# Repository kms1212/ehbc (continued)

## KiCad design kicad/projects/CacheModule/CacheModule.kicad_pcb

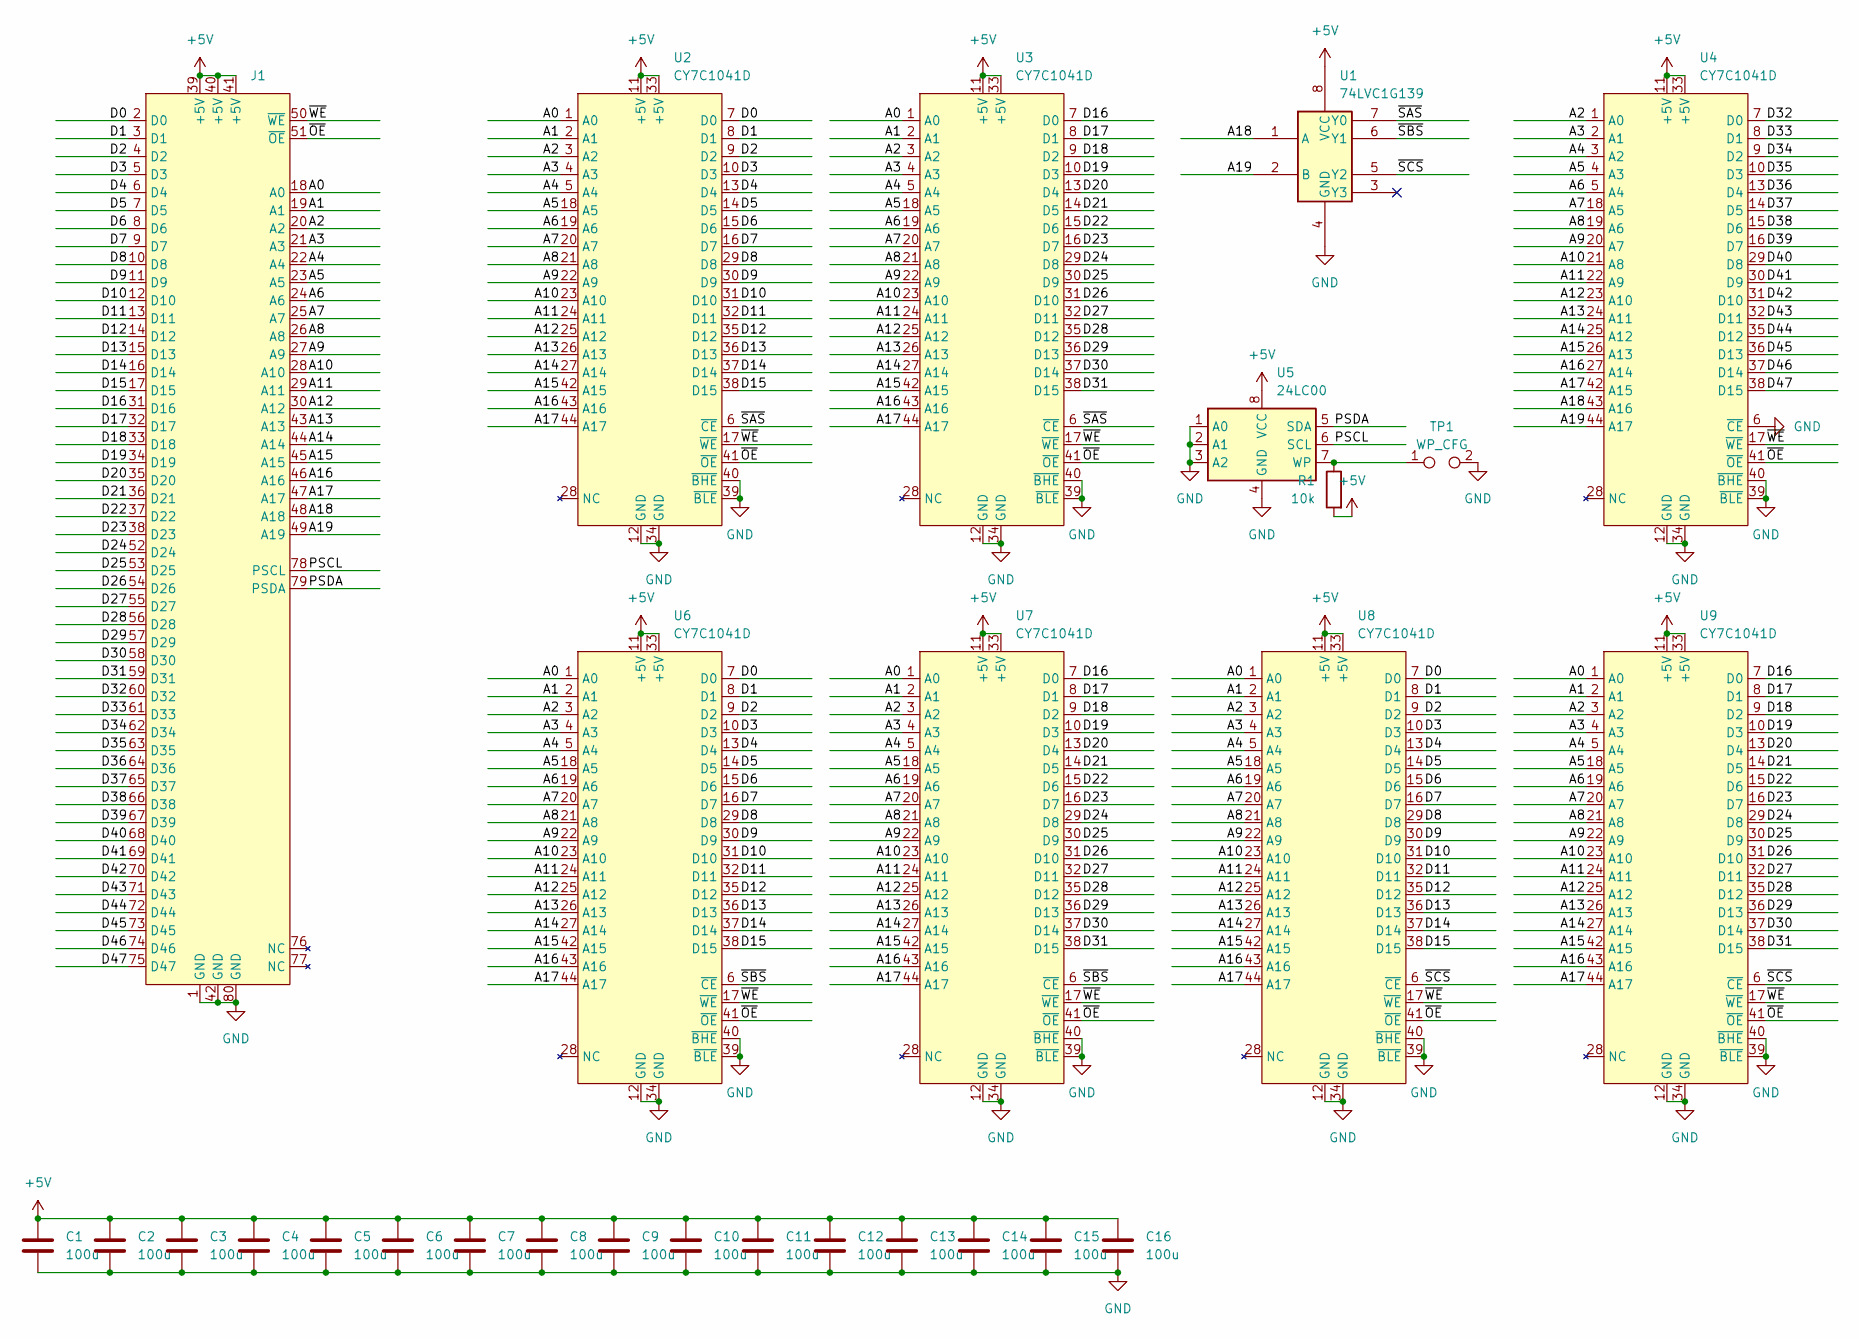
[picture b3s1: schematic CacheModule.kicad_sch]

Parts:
C1, C2, C3, C4, C5, C6, C7, C8, C9, C10, C11, C12, C13, C14, C15, C16: 100u; C_0603_1608Metric_Pad1.08x0.95mm_HandSolder
J1: SIMM80_CardEdge
R1: 10k; R_0603_1608Metric_Pad0.98x0.95mm_HandSolder
TP1: WP_CFG; R_0402_1005Metric
U1: 74LVC1G139; SSOP-8_3.9x5.05mm_P1.27mm
U2, U3, U4, U6, U7, U8, U9: CY7C1041D; TSOP-II-44_10.16x18.41mm_P0.8mm
U5: 24LC00; SOIC-8_3.9x4.9mm_P1.27mm

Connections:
+5V: C1.1, C2.1, C3.1, C4.1, C5.1, C6.1, C7.1, C8.1, C9.1, C10.1, C11.1, C12.1, C13.1, C14.1, C15.1, C16.1, J1.39 (+5V), J1.40 (+5V), J1.41 (+5V), R1.2, U1.8 (VCC), U2.11 (+5V), U2.33 (+5V), U3.11 (+5V), U3.33 (+5V), U4.11 (+5V), U4.33 (+5V), U5.8 (VCC), U6.11 (+5V), U6.33 (+5V), U7.11 (+5V), U7.33 (+5V), U8.11 (+5V), U8.33 (+5V), U9.11 (+5V), U9.33 (+5V)
/A0: J1.18 (A0), U2.1 (A0), U3.1 (A0), U6.1 (A0), U7.1 (A0), U8.1 (A0), U9.1 (A0)
/A1: J1.19 (A1), U2.2 (A1), U3.2 (A1), U6.2 (A1), U7.2 (A1), U8.2 (A1), U9.2 (A1)
/A2: J1.20 (A2), U2.3 (A2), U3.3 (A2), U4.1 (A0), U6.3 (A2), U7.3 (A2), U8.3 (A2), U9.3 (A2)
/A3: J1.21 (A3), U2.4 (A3), U3.4 (A3), U4.2 (A1), U6.4 (A3), U7.4 (A3), U8.4 (A3), U9.4 (A3)
/A4: J1.22 (A4), U2.5 (A4), U3.5 (A4), U4.3 (A2), U6.5 (A4), U7.5 (A4), U8.5 (A4), U9.5 (A4)
/A5: J1.23 (A5), U2.18 (A5), U3.18 (A5), U4.4 (A3), U6.18 (A5), U7.18 (A5), U8.18 (A5), U9.18 (A5)
/A6: J1.24 (A6), U2.19 (A6), U3.19 (A6), U4.5 (A4), U6.19 (A6), U7.19 (A6), U8.19 (A6), U9.19 (A6)
/A7: J1.25 (A7), U2.20 (A7), U3.20 (A7), U4.18 (A5), U6.20 (A7), U7.20 (A7), U8.20 (A7), U9.20 (A7)
/A8: J1.26 (A8), U2.21 (A8), U3.21 (A8), U4.19 (A6), U6.21 (A8), U7.21 (A8), U8.21 (A8), U9.21 (A8)
/A9: J1.27 (A9), U2.22 (A9), U3.22 (A9), U4.20 (A7), U6.22 (A9), U7.22 (A9), U8.22 (A9), U9.22 (A9)
/A10: J1.28 (A10), U2.23 (A10), U3.23 (A10), U4.21 (A8), U6.23 (A10), U7.23 (A10), U8.23 (A10), U9.23 (A10)
/A11: J1.29 (A11), U2.24 (A11), U3.24 (A11), U4.22 (A9), U6.24 (A11), U7.24 (A11), U8.24 (A11), U9.24 (A11)
/A12: J1.30 (A12), U2.25 (A12), U3.25 (A12), U4.23 (A10), U6.25 (A12), U7.25 (A12), U8.25 (A12), U9.25 (A12)
/A13: J1.43 (A13), U2.26 (A13), U3.26 (A13), U4.24 (A11), U6.26 (A13), U7.26 (A13), U8.26 (A13), U9.26 (A13)
/A14: J1.44 (A14), U2.27 (A14), U3.27 (A14), U4.25 (A12), U6.27 (A14), U7.27 (A14), U8.27 (A14), U9.27 (A14)
/A15: J1.45 (A15), U2.42 (A15), U3.42 (A15), U4.26 (A13), U6.42 (A15), U7.42 (A15), U8.42 (A15), U9.42 (A15)
/A16: J1.46 (A16), U2.43 (A16), U3.43 (A16), U4.27 (A14), U6.43 (A16), U7.43 (A16), U8.43 (A16), U9.43 (A16)
/A17: J1.47 (A17), U2.44 (A17), U3.44 (A17), U4.42 (A15), U6.44 (A17), U7.44 (A17), U8.44 (A17), U9.44 (A17)
/A18: J1.48 (A18), U1.1 (A), U4.43 (A16)
/A19: J1.49 (A19), U1.2 (B), U4.44 (A17)
/D0: J1.2 (D0), U2.7 (D0), U6.7 (D0), U8.7 (D0)
/D1: J1.3 (D1), U2.8 (D1), U6.8 (D1), U8.8 (D1)
/D2: J1.4 (D2), U2.9 (D2), U6.9 (D2), U8.9 (D2)
/D3: J1.5 (D3), U2.10 (D3), U6.10 (D3), U8.10 (D3)
/D4: J1.6 (D4), U2.13 (D4), U6.13 (D4), U8.13 (D4)
/D5: J1.7 (D5), U2.14 (D5), U6.14 (D5), U8.14 (D5)
/D6: J1.8 (D6), U2.15 (D6), U6.15 (D6), U8.15 (D6)
/D7: J1.9 (D7), U2.16 (D7), U6.16 (D7), U8.16 (D7)
/D8: J1.10 (D8), U2.29 (D8), U6.29 (D8), U8.29 (D8)
/D9: J1.11 (D9), U2.30 (D9), U6.30 (D9), U8.30 (D9)
/D10: J1.12 (D10), U2.31 (D10), U6.31 (D10), U8.31 (D10)
/D11: J1.13 (D11), U2.32 (D11), U6.32 (D11), U8.32 (D11)
/D12: J1.14 (D12), U2.35 (D12), U6.35 (D12), U8.35 (D12)
/D13: J1.15 (D13), U2.36 (D13), U6.36 (D13), U8.36 (D13)
/D14: J1.16 (D14), U2.37 (D14), U6.37 (D14), U8.37 (D14)
/D15: J1.17 (D15), U2.38 (D15), U6.38 (D15), U8.38 (D15)
/D16: J1.31 (D16), U3.7 (D0), U7.7 (D0), U9.7 (D0)
/D17: J1.32 (D17), U3.8 (D1), U7.8 (D1), U9.8 (D1)
/D18: J1.33 (D18), U3.9 (D2), U7.9 (D2), U9.9 (D2)
/D19: J1.34 (D19), U3.10 (D3), U7.10 (D3), U9.10 (D3)
/D20: J1.35 (D20), U3.13 (D4), U7.13 (D4), U9.13 (D4)
/D21: J1.36 (D21), U3.14 (D5), U7.14 (D5), U9.14 (D5)
/D22: J1.37 (D22), U3.15 (D6), U7.15 (D6), U9.15 (D6)
/D23: J1.38 (D23), U3.16 (D7), U7.16 (D7), U9.16 (D7)
/D24: J1.52 (D24), U3.29 (D8), U7.29 (D8), U9.29 (D8)
/D25: J1.53 (D25), U3.30 (D9), U7.30 (D9), U9.30 (D9)
/D26: J1.54 (D26), U3.31 (D10), U7.31 (D10), U9.31 (D10)
/D27: J1.55 (D27), U3.32 (D11), U7.32 (D11), U9.32 (D11)
/D28: J1.56 (D28), U3.35 (D12), U7.35 (D12), U9.35 (D12)
/D29: J1.57 (D29), U3.36 (D13), U7.36 (D13), U9.36 (D13)
/D30: J1.58 (D30), U3.37 (D14), U7.37 (D14), U9.37 (D14)
/D31: J1.59 (D31), U3.38 (D15), U7.38 (D15), U9.38 (D15)
/D32: J1.60 (D32), U4.7 (D0)
/D33: J1.61 (D33), U4.8 (D1)
/D34: J1.62 (D34), U4.9 (D2)
/D35: J1.63 (D35), U4.10 (D3)
/D36: J1.64 (D36), U4.13 (D4)
/D37: J1.65 (D37), U4.14 (D5)
/D38: J1.66 (D38), U4.15 (D6)
/D39: J1.67 (D39), U4.16 (D7)
/D40: J1.68 (D40), U4.29 (D8)
/D41: J1.69 (D41), U4.30 (D9)
/D42: J1.70 (D42), U4.31 (D10)
/D43: J1.71 (D43), U4.32 (D11)
/D44: J1.72 (D44), U4.35 (D12)
/D45: J1.73 (D45), U4.36 (D13)
/D46: J1.74 (D46), U4.37 (D14)
/D47: J1.75 (D47), U4.38 (D15)
/PSCL: J1.78 (PSCL), U5.6 (SCL)
/PSDA: J1.79 (PSDA), U5.5 (SDA)
/~OE: J1.51 (~OE), U2.41 (~OE), U3.41 (~OE), U4.41 (~OE), U6.41 (~OE), U7.41 (~OE), U8.41 (~OE), U9.41 (~OE)
/~SAS: U1.7 (Y0), U2.6 (~CE), U3.6 (~CE)
/~SBS: U1.6 (Y1), U6.6 (~CE), U7.6 (~CE)
/~SCS: U1.5 (Y2), U8.6 (~CE), U9.6 (~CE)
/~WE: J1.50 (~WE), U2.17 (~WE), U3.17 (~WE), U4.17 (~WE), U6.17 (~WE), U7.17 (~WE), U8.17 (~WE), U9.17 (~WE)
GND: C1.2, C2.2, C3.2, C4.2, C5.2, C6.2, C7.2, C8.2, C9.2, C10.2, C11.2, C12.2, C13.2, C14.2, C15.2, C16.2, J1.1 (GND), J1.42 (GND), J1.80 (GND), TP1.2, U1.4 (GND), U2.12 (GND), U2.34 (GND), U2.39 (~BLE), U2.40 (~BHE), U3.12 (GND), U3.34 (GND), U3.39 (~BLE), U3.40 (~BHE), U4.6 (~CE), U4.12 (GND), U4.34 (GND), U4.39 (~BLE), U4.40 (~BHE), U5.1 (A0), U5.2 (A1), U5.3 (A2), U5.4 (GND), U6.12 (GND), U6.34 (GND), U6.39 (~BLE), U6.40 (~BHE), U7.12 (GND), U7.34 (GND), U7.39 (~BLE), U7.40 (~BHE), U8.12 (GND), U8.34 (GND), U8.39 (~BLE), U8.40 (~BHE), U9.12 (GND), U9.34 (GND), U9.39 (~BLE), U9.40 (~BHE)
unnamed: R1.1, TP1.1, U5.7 (WP)

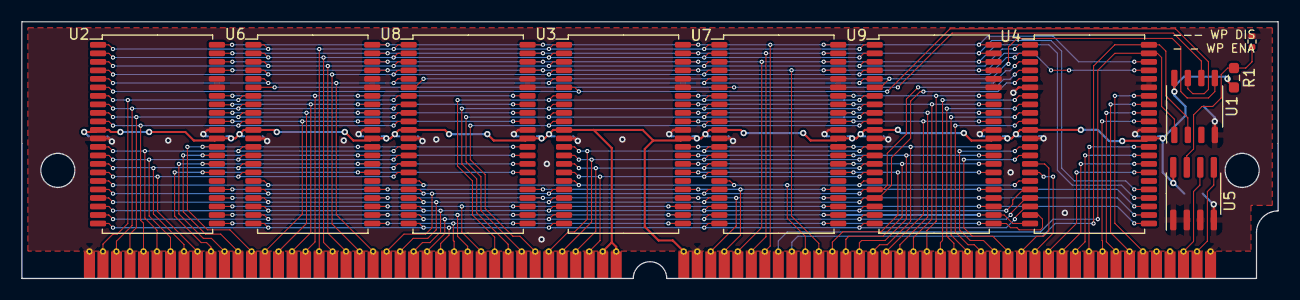
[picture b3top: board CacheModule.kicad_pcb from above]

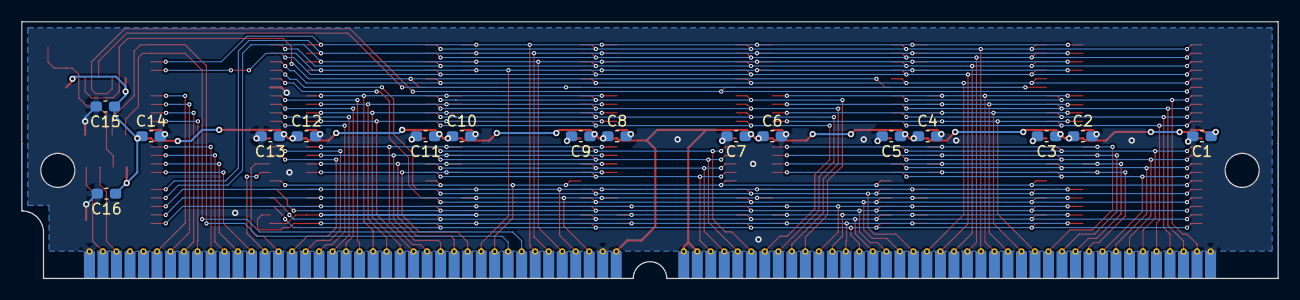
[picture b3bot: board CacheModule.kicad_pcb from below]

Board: 2 copper layers, 118.1 x 24.1 mm, 28 parts (16 on the bottom side), 78 nets.

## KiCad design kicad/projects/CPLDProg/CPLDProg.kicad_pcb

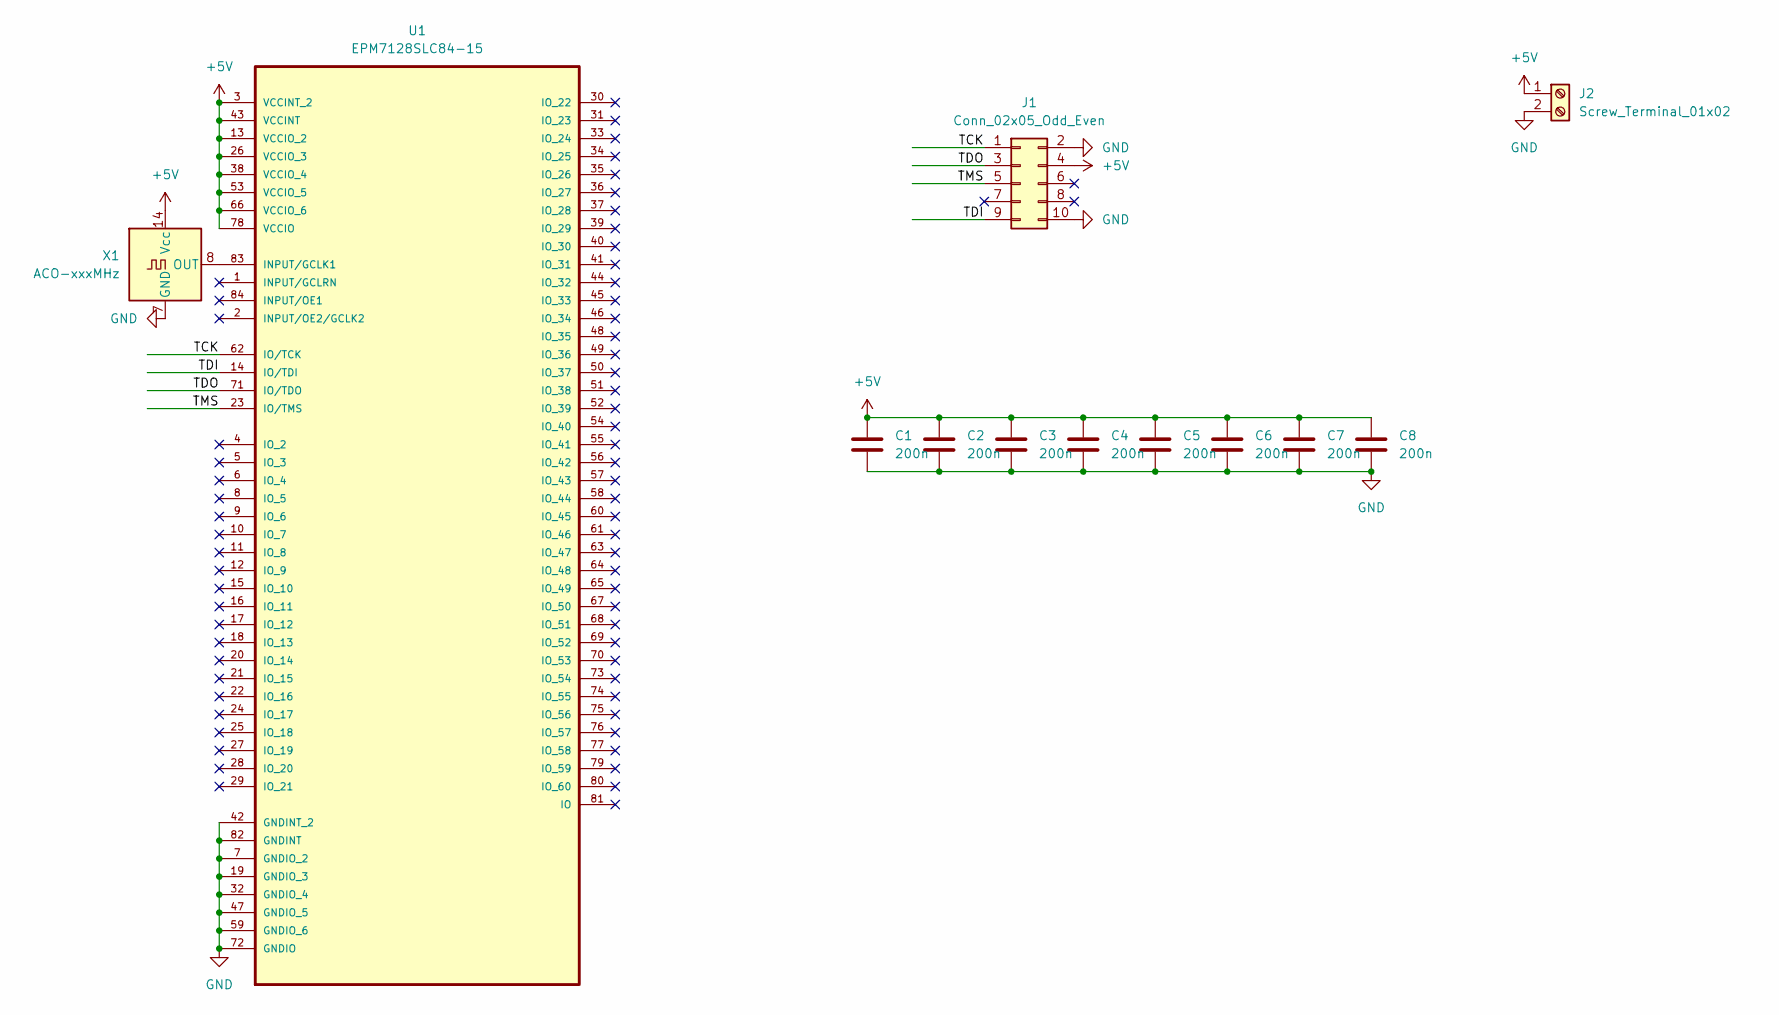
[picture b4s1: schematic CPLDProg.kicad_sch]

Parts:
C1, C2, C3, C4, C5, C6, C7, C8: 200n; C_Disc_D3.0mm_W1.6mm_P2.50mm
J1: Conn_02x05_Odd_Even; IDC-Header_2x05_P2.54mm_Vertical
J2: Screw_Terminal_01x02; TerminalBlock_Altech_AK300-2_P5.00mm
U1: EPM7128SLC84-15; PLCC-84_THT-Socket; MPN EPM7128SLC84-15
X1: ACO-xxxMHz; Oscillator_DIP-14

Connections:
+5V: C1.2, C2.2, C3.2, C4.2, C5.2, C6.2, C7.2, C8.2, J1.4, J2.1, U1.3 (VCCINT_2), U1.13 (VCCIO_2), U1.26 (VCCIO_3), U1.38 (VCCIO_4), U1.43 (VCCINT), U1.53 (VCCIO_5), U1.66 (VCCIO_6), U1.78 (VCCIO), X1.14 (Vcc)
/TCK: J1.1, U1.62 (IO/TCK)
/TDI: J1.9, U1.14 (IO/TDI)
/TDO: J1.3, U1.71 (IO/TDO)
/TMS: J1.5, U1.23 (IO/TMS)
GND: C1.1, C2.1, C3.1, C4.1, C5.1, C6.1, C7.1, C8.1, J1.2, J1.10, J2.2, U1.7 (GNDIO_2), U1.19 (GNDIO_3), U1.32 (GNDIO_4), U1.42 (GNDINT_2), U1.47 (GNDIO_5), U1.59 (GNDIO_6), U1.72 (GNDIO), U1.82 (GNDINT), X1.7 (GND)
unnamed: U1.83 (INPUT/GCLK1), X1.8 (OUT)

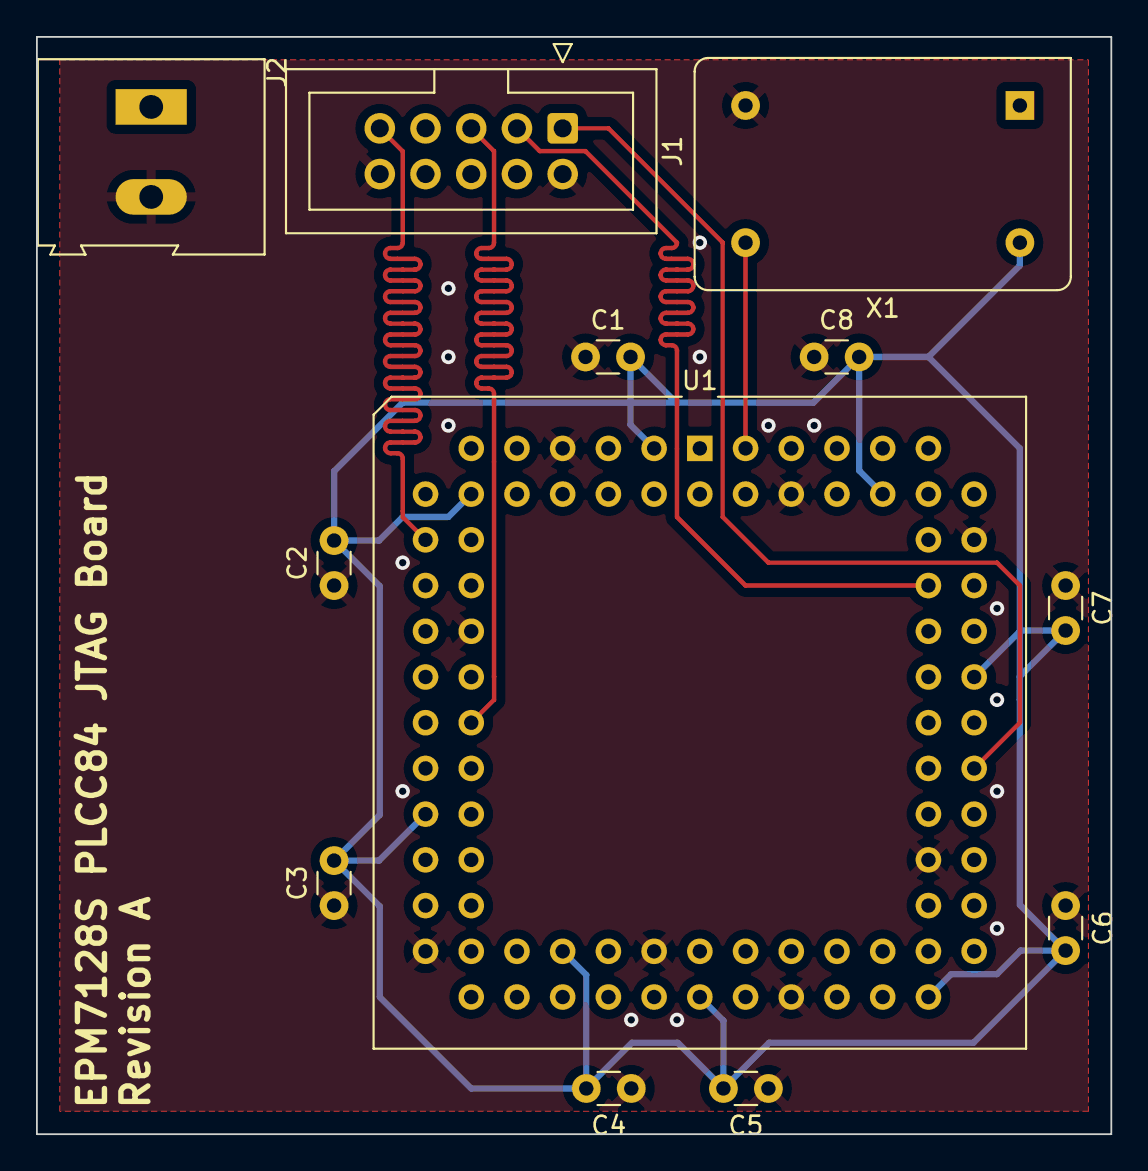
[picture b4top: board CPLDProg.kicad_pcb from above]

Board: 2 copper layers, 59.7 x 61.0 mm, 12 parts (0 on the bottom side), 7 nets.

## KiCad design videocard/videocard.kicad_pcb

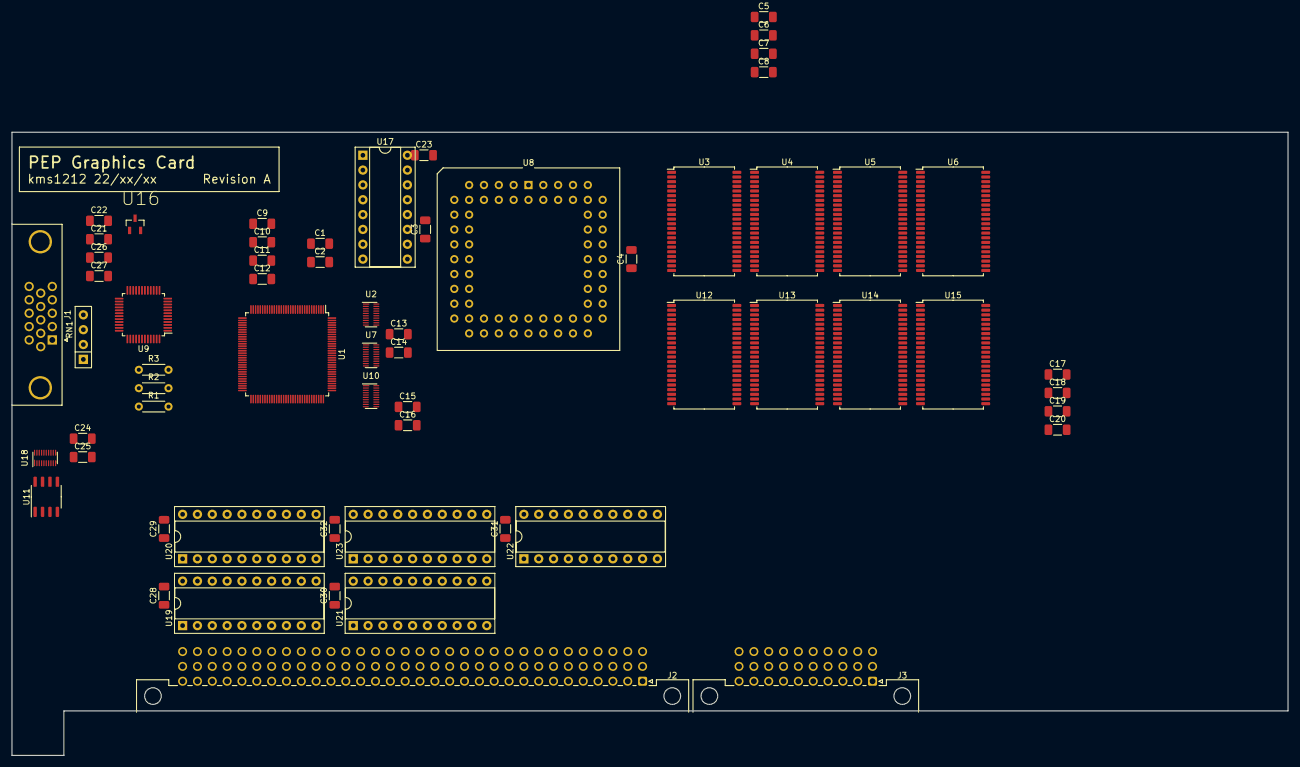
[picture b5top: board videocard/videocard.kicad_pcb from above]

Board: 4 copper layers, 218.4 x 106.7 mm, 62 parts (0 on the bottom side), 159 nets, no tracks yet.

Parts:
C1, C2, C3, C4, C5, C6, C7, C8, C11, C12, C13, C14, C15, C16, C17, C18, C19, C20, C21, C23, C24, C25, C26, C28, C29, C30, C31, C32: 100n; C_1206_3216Metric_Pad1.33x1.80mm_HandSolder
C9, C10, C22: 1u; C_1206_3216Metric_Pad1.33x1.80mm_HandSolder
C27: 10n; C_1206_3216Metric_Pad1.33x1.80mm_HandSolder
J1: DE15_Receptacle_HighDensity_MountingHoles; DSUB-15-HD_Female_Horizontal_P2.29x1.98mm_EdgePinOffset3.03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
J2: PEP_Data_DIN41612_3x32; DIN41612_C_3x32_Male_Horizontal_THT
J3: PEP_Power_DIN41612_3x10; DIN41612_C3_3x10_Male_Horizontal_THT
R1: 200k; R_Axial_DIN0204_L3.6mm_D1.6mm_P5.08mm_Horizontal
R2: 1k; R_Axial_DIN0204_L3.6mm_D1.6mm_P5.08mm_Horizontal
R3: 530; R_Axial_DIN0204_L3.6mm_D1.6mm_P5.08mm_Horizontal
RN1: 75; R_Array_SIP4
U1: SSD1963QL9; LQFP-128_14x14mm_P0.4mm
U2, U7, U10, U18: TXB0108DQSR; USON-20_2x4mm_P0.4mm
U3, U4, U5, U6, U12, U13, U14, U15: CY7C1041D; TSOP-II-44_10.16x18.41mm_P0.8mm
U8: MC68000FN; PLCC-68_THT-Socket
U9: ADV7123; LQFP-48_7x7mm_P0.5mm
U11: PCA9306D; SO-8_3.9x4.9mm_P1.27mm
U16: AD1580BRTZ-REEL7; SOT96P237X112-3N
U17: 74LS137; DIP-16_W7.62mm_Socket
U19, U21, U22: 74LS573; DIP-20_W7.62mm_Socket
U20, U23: 74LS245; DIP-20_W7.62mm_Socket

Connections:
+1V2: C9.1, C12.1, U1.1 (VDDD_1), U1.6 (VDDD_1), U1.14 (VDDD_1), U1.18 (VDDPLL), U1.21 (VDDD_1), U1.25 (VDDD_1), U1.32 (VDDD_1), U1.40 (VDDD_1), U1.46 (VDDD_1), U1.56 (VDDD_1), U1.64 (VDDD_2), U1.73 (VDDD_2), U1.82 (VDDD_2), U1.93 (VDDD_2), U1.102 (VDDD_2), U1.110 (VDDD_2), U1.119 (VDDD_2), U1.126 (VDDD_2)
+3.3V: C2.1, C10.1, C11.1, C14.1, C16.1, C25.1, J3.a8 (+3.3V), J3.a9 (+3.3V), J3.b8 (+3.3V), J3.b9 (+3.3V), J3.c8 (+3.3V), J3.c9 (+3.3V), U1.4 (VDDIO), U1.12 (VDDIO), U1.16 (VDDIO), U1.27 (VDDLCD), U1.34 (VDDLCD), U1.42 (VDDLCD), U1.48 (VDDLCD), U1.54 (VDDLCD), U1.58 (VDDLCD), U1.66 (VDDLCD), U1.75 (VDDLCD), U1.84 (VDDLCD), U1.95 (VDDIO), U1.97 (VDDIO), U1.100 (VDDIO), U1.108 (VDDIO), U1.117 (VDDIO), U1.124 (VDDIO), U2.5 (VCCA), U7.5 (VCCA), U10.5 (VCCA), U11.2 (VREF1), U18.5 (VCCA)
+3.3VA: C21.2, C26.1, C27.1, R2.1, U9.13 (VAA), U9.29 (VAA), U9.30 (VAA)
+5V: C1.1, C3.1, C4.1, C5.1, C6.1, C7.1, C8.1, C13.1, C15.1, C17.1, C18.1, C19.1, C20.1, C23.1, C24.1, C28.2, C29.2, C30.2, C31.2, C32.2, J3.a5 (+5V), J3.a6 (+5V), J3.a7 (+5V), J3.b7 (+5V), J3.c5 (+5V), J3.c6 (+5V), J3.c7 (+5V), R1.1, U2.16 (VCCB), U3.11 (+5V), U3.33 (+5V), U4.11 (+5V), U4.33 (+5V), U5.11 (+5V), U5.33 (+5V), U6.11 (+5V), U6.33 (+5V), U7.16 (VCCB), U8.14 (VCC), U8.52 (VCC), U10.16 (VCCB), U12.11 (+5V), U12.33 (+5V), U13.11 (+5V), U13.33 (+5V), U14.11 (+5V), U14.33 (+5V), U15.11 (+5V), U15.33 (+5V), U17.16 (VCC), U18.16 (VCCB), U19.20 (VCC), U20.20 (VCC), U21.20 (VCC), U22.20 (VCC), U23.20 (VCC)
+12V: J3.a2 (+12V), J3.a3 (+12V), J3.b2 (+12V), J3.b3 (+12V), J3.c2 (+12V), J3.c3 (+12V)
/33A1: U1.122 (~D/C), U10.1 (A1)
/33D0: U1.7 (D0), U2.1 (A1)
/33D1: U1.8 (D1), U2.2 (A2)
/33D2: U1.9 (D2), U2.3 (A3)
/33D3: U1.10 (D3), U2.4 (A4)
/33D4: U1.11 (D4), U2.7 (A5)
/33D5: U1.116 (D5), U2.8 (A6)
/33D6: U1.115 (D6), U2.9 (A7)
/33D7: U1.114 (D7), U2.10 (A8)
/33D8: U1.113 (D8), U7.1 (A1)
/33D9: U1.112 (D9), U7.2 (A2)
/33D10: U1.111 (D10), U7.3 (A3)
/33D11: U1.107 (D11), U7.4 (A4)
/33D12: U1.106 (D12), U7.7 (A5)
/33D13: U1.105 (D13), U7.8 (A6)
/33D14: U1.104 (D14), U7.9 (A7)
/33D15: U1.103 (D15), U7.10 (A8)
/33DDCSCL: U1.37 (GPIO1), U11.3 (SCL1)
/33DDCSDA: U1.38 (GPIO2), U11.4 (SDA1)
/33E: U1.121 (E/~RD), U10.2 (A2)
/33HSYNC: U1.44 (LLINE), U18.2 (A2)
/33R/~W: U1.120 (R/~W~{/~{WR), U10.3 (A3)
/33VSYNC: U1.43 (LFRAME), U18.1 (A1)
/A1: U3.1 (A0), U4.1 (A0), U5.1 (A0), U6.1 (A0), U8.32 (A1), U10.20 (B1), U12.1 (A0), U13.1 (A0), U14.1 (A0), U15.1 (A0), U19.13 (Q6)
/A2: U3.2 (A1), U4.2 (A1), U5.2 (A1), U6.2 (A1), U8.33 (A2), U12.2 (A1), U13.2 (A1), U14.2 (A1), U15.2 (A1), U19.14 (Q5)
/A3: U3.3 (A2), U4.3 (A2), U5.3 (A2), U6.3 (A2), U8.34 (A3), U12.3 (A2), U13.3 (A2), U14.3 (A2), U15.3 (A2), U19.15 (Q4)
/A4: U3.4 (A3), U4.4 (A3), U5.4 (A3), U6.4 (A3), U8.35 (A4), U12.4 (A3), U13.4 (A3), U14.4 (A3), U15.4 (A3), U19.16 (Q3)
/A5: U3.5 (A4), U4.5 (A4), U5.5 (A4), U6.5 (A4), U8.36 (A5), U12.5 (A4), U13.5 (A4), U14.5 (A4), U15.5 (A4), U19.17 (Q2)
/A6: U3.18 (A5), U4.18 (A5), U5.18 (A5), U6.18 (A5), U8.37 (A6), U12.18 (A5), U13.18 (A5), U14.18 (A5), U15.18 (A5), U19.18 (Q1)
/A7: U3.19 (A6), U4.19 (A6), U5.19 (A6), U6.19 (A6), U8.38 (A7), U12.19 (A6), U13.19 (A6), U14.19 (A6), U15.19 (A6), U19.19 (Q0)
/A8: U3.20 (A7), U4.20 (A7), U5.20 (A7), U6.20 (A7), U8.39 (A8), U12.20 (A7), U13.20 (A7), U14.20 (A7), U15.20 (A7), U21.12 (Q7)
/A9: U3.21 (A8), U4.21 (A8), U5.21 (A8), U6.21 (A8), U8.40 (A9), U12.21 (A8), U13.21 (A8), U14.21 (A8), U15.21 (A8), U21.13 (Q6)
/A10: U3.22 (A9), U4.22 (A9), U5.22 (A9), U6.22 (A9), U8.41 (A10), U12.22 (A9), U13.22 (A9), U14.22 (A9), U15.22 (A9), U21.14 (Q5)
/A11: U3.23 (A10), U4.23 (A10), U5.23 (A10), U6.23 (A10), U8.42 (A11), U12.23 (A10), U13.23 (A10), U14.23 (A10), U15.23 (A10), U21.15 (Q4)
/A12: U3.24 (A11), U4.24 (A11), U5.24 (A11), U6.24 (A11), U8.43 (A12), U12.24 (A11), U13.24 (A11), U14.24 (A11), U15.24 (A11), U21.16 (Q3)
/A13: U3.25 (A12), U4.25 (A12), U5.25 (A12), U6.25 (A12), U8.44 (A13), U12.25 (A12), U13.25 (A12), U14.25 (A12), U15.25 (A12), U21.17 (Q2)
/A14: U3.26 (A13), U4.26 (A13), U5.26 (A13), U6.26 (A13), U8.45 (A14), U12.26 (A13), U13.26 (A13), U14.26 (A13), U15.26 (A13), U21.18 (Q1)
/A15: U3.27 (A14), U4.27 (A14), U5.27 (A14), U6.27 (A14), U8.46 (A15), U12.27 (A14), U13.27 (A14), U14.27 (A14), U15.27 (A14), U21.19 (Q0)
/A16: U3.42 (A15), U4.42 (A15), U5.42 (A15), U6.42 (A15), U8.47 (A16), U12.42 (A15), U13.42 (A15), U14.42 (A15), U15.42 (A15), U22.16 (Q3)
/A17: U3.43 (A16), U4.43 (A16), U5.43 (A16), U6.43 (A16), U8.48 (A17), U12.43 (A16), U13.43 (A16), U14.43 (A16), U15.43 (A16), U22.17 (Q2)
/A18: U3.44 (A17), U4.44 (A17), U5.44 (A17), U6.44 (A17), U8.49 (A18), U12.44 (A17), U13.44 (A17), U14.44 (A17), U15.44 (A17), U22.18 (Q1)
/A19: U8.50 (A19), U17.1 (A0), U22.19 (Q0)
/A20: U8.51 (A20), U17.2 (A1), U22.12 (Q7)
/A21: U8.53 (A21), U17.3 (A2), U22.13 (Q6)
/A22: U8.54 (A22), U22.14 (Q5)
/A23: U8.55 (A23), U22.15 (Q4)
/B0: U1.81 (LDATA0), U9.16 (B2)
/B1: U1.80 (LDATA1), U9.17 (B3)
/B2: U1.79 (LDATA2), U9.18 (B4)
/B3: U1.78 (LDATA3), U9.19 (B5)
/B4: U1.77 (LDATA4), U9.20 (B6)
/B5: U1.76 (LDATA5), U9.21 (B7)
/B6: U1.72 (LDATA6), U9.22 (B8)
/B7: U1.71 (LDATA7), U9.23 (B9)
/BAO: J1.3, RN1.4 (R3), U9.28 (IOB)
/D0: U2.20 (B1), U3.7 (D0), U4.7 (D0), U5.7 (D0), U6.7 (D0), U8.5 (D0), U12.7 (D0), U13.7 (D0), U14.7 (D0), U15.7 (D0), U20.18 (B0)
/D1: U2.19 (B2), U3.8 (D1), U4.8 (D1), U5.8 (D1), U6.8 (D1), U8.4 (D1), U12.8 (D1), U13.8 (D1), U14.8 (D1), U15.8 (D1), U20.17 (B1)
/D2: U2.18 (B3), U3.9 (D2), U4.9 (D2), U5.9 (D2), U6.9 (D2), U8.3 (D2), U12.9 (D2), U13.9 (D2), U14.9 (D2), U15.9 (D2), U20.16 (B2)
/D3: U2.17 (B4), U3.10 (D3), U4.10 (D3), U5.10 (D3), U6.10 (D3), U8.2 (D3), U12.10 (D3), U13.10 (D3), U14.10 (D3), U15.10 (D3), U20.15 (B3)
/D4: U2.14 (B5), U3.13 (D4), U4.13 (D4), U5.13 (D4), U6.13 (D4), U8.1 (D4), U12.13 (D4), U13.13 (D4), U14.13 (D4), U15.13 (D4), U20.14 (B4)
/D5: U2.13 (B6), U3.14 (D5), U4.14 (D5), U5.14 (D5), U6.14 (D5), U8.68 (D5), U12.14 (D5), U13.14 (D5), U14.14 (D5), U15.14 (D5), U20.13 (B5)
/D6: U2.12 (B7), U3.15 (D6), U4.15 (D6), U5.15 (D6), U6.15 (D6), U8.67 (D6), U12.15 (D6), U13.15 (D6), U14.15 (D6), U15.15 (D6), U20.12 (B6)
/D7: U2.11 (B8), U3.16 (D7), U4.16 (D7), U5.16 (D7), U6.16 (D7), U8.66 (D7), U12.16 (D7), U13.16 (D7), U14.16 (D7), U15.16 (D7), U20.11 (B7)
/D8: U3.29 (D8), U4.29 (D8), U5.29 (D8), U6.29 (D8), U7.20 (B1), U8.65 (D8), U12.29 (D8), U13.29 (D8), U14.29 (D8), U15.29 (D8), U23.18 (B0)
/D9: U3.30 (D9), U4.30 (D9), U5.30 (D9), U6.30 (D9), U7.19 (B2), U8.64 (D9), U12.30 (D9), U13.30 (D9), U14.30 (D9), U15.30 (D9), U23.17 (B1)
/D10: U3.31 (D10), U4.31 (D10), U5.31 (D10), U6.31 (D10), U7.18 (B3), U8.63 (D10), U12.31 (D10), U13.31 (D10), U14.31 (D10), U15.31 (D10), U23.16 (B2)
/D11: U3.32 (D11), U4.32 (D11), U5.32 (D11), U6.32 (D11), U7.17 (B4), U8.62 (D11), U12.32 (D11), U13.32 (D11), U14.32 (D11), U15.32 (D11), U23.15 (B3)
/D12: U3.35 (D12), U4.35 (D12), U5.35 (D12), U6.35 (D12), U7.14 (B5), U8.61 (D12), U12.35 (D12), U13.35 (D12), U14.35 (D12), U15.35 (D12), U23.14 (B4)
/D13: U3.36 (D13), U4.36 (D13), U5.36 (D13), U6.36 (D13), U7.13 (B6), U8.60 (D13), U12.36 (D13), U13.36 (D13), U14.36 (D13), U15.36 (D13), U23.13 (B5)
/D14: U3.37 (D14), U4.37 (D14), U5.37 (D14), U6.37 (D14), U7.12 (B7), U8.59 (D14), U12.37 (D14), U13.37 (D14), U14.37 (D14), U15.37 (D14), U23.12 (B6)
/D15: U3.38 (D15), U4.38 (D15), U5.38 (D15), U6.38 (D15), U7.11 (B8), U8.58 (D15), U12.38 (D15), U13.38 (D15), U14.38 (D15), U15.38 (D15), U23.11 (B7)
/DDCSCL: J1.15, U11.6 (SCL2)
/DDCSDA: J1.12, U11.5 (SDA2)
/E: U8.22 (E), U10.19 (B2)
/G0: U1.70 (LDATA8), U9.3 (G2)
/G1: U1.69 (LDATA9), U9.4 (G3)
/G2: U1.68 (LDATA10), U9.5 (G4)
/G3: U1.67 (LDATA11), U9.6 (G5)
/G4: U1.63 (LDATA12), U9.7 (G6)
/G5: U1.62 (LDATA13), U9.8 (G7)
/G6: U1.61 (LDATA14), U9.9 (G8)
/G7: U1.60 (LDATA15), U9.10 (G9)
/GAO: J1.2, RN1.3 (R2), U9.32 (IOG)
/HSYNC: J1.13, U18.19 (B2)
/PA0: J2.b24 (A0), U19.9 (D7)
/PA1: J2.b25 (A1), U19.8 (D6)
/PA2: J2.b26 (A2), U19.7 (D5)
/PA3: J2.b27 (A3), U19.6 (D4)
/PA4: J2.b28 (A4), U19.5 (D3)
/PA5: J2.b29 (A5), U19.4 (D2)
/PA6: J2.b30 (A6), U19.3 (D1)
/PA7: J2.b31 (A7), U19.2 (D0)
/PA8: J2.b15 (A8), U21.9 (D7)
/PA9: J2.b16 (A9), U21.8 (D6)
/PA10: J2.b17 (A10), U21.7 (D5)
/PA11: J2.b18 (A11), U21.6 (D4)
/PA12: J2.b19 (A12), U21.5 (D3)
/PA13: J2.b20 (A13), U21.4 (D2)
/PA14: J2.b21 (A14), U21.3 (D1)
/PA15: J2.b22 (A15), U21.2 (D0)
/PA16: J2.b10 (A16), U22.5 (D3)
/PA17: J2.b11 (A17), U22.4 (D2)
/PA18: J2.b12 (A18), U22.3 (D1)
/PA19: J2.b13 (A19), U22.2 (D0)
/PA20: J2.b6 (A20), U22.9 (D7)
/PA21: J2.b7 (A21), U22.8 (D6)
/PA22: J2.b8 (A22), U22.7 (D5)
/PA23: J2.b9 (A23), U22.6 (D4)
/PD0: J2.c25 (D16), U20.2 (A0)
/PD1: J2.c24 (D17), U20.3 (A1)
/PD2: J2.c23 (D18), U20.4 (A2)
/PD3: J2.c22 (D19), U20.5 (A3)
/PD4: J2.c21 (D20), U20.6 (A4)
/PD5: J2.c20 (D21), U20.7 (A5)
/PD6: J2.c19 (D22), U20.8 (A6)
/PD7: J2.c18 (D23), U20.9 (A7)
/PD8: J2.c16 (D24), U23.2 (A0)
/PD9: J2.c15 (D25), U23.3 (A1)
/PD10: J2.c14 (D26), U23.4 (A2)
/PD11: J2.c13 (D27), U23.5 (A3)
/PD12: J2.c12 (D28), U23.6 (A4)
/PD13: J2.c11 (D29), U23.7 (A5)
/PD14: J2.c10 (D30), U23.8 (A6)
/PD15: J2.c9 (D31), U23.9 (A7)
/PXCLK: U1.45 (LSHIFT), U9.24 (CLOCK)
/R0: U1.59 (LDATA16), U9.41 (R2)
/R1: U1.35 (LDATA17), U9.42 (R3)
/R2: U1.86 (LDATA18), U9.43 (R4)
/R3: U1.85 (LDATA19), U9.44 (R5)
/R4: U1.31 (LDATA20), U9.45 (R6)
/R5: U1.30 (LDATA21), U9.46 (R7)
/R6: U1.29 (LDATA22), U9.47 (R8)
/R7: U1.28 (LDATA23), U9.48 (R9)
/RAO: J1.1, RN1.2 (R1), U9.34 (IOR)
/R/~W: U8.9 (R/W), U10.18 (B3)
/VSYNC: J1.14, U18.20 (B1)
/~BLANK: U1.49 (LDEN), U9.11 (~BLANK)
/~LDS: U3.39 (~BLE), U4.39 (~BLE), U5.39 (~BLE), U6.39 (~BLE), U8.8 (LDS), U12.39 (~BLE), U13.39 (~BLE), U14.39 (~BLE), U15.39 (~BLE)
/~PSAVE: U1.36 (GPIO0), U9.38 (~PSAVE)
/~UDS: U3.40 (~BHE), U4.40 (~BHE), U5.40 (~BHE), U6.40 (~BHE), U8.7 (UDS), U12.40 (~BHE), U13.40 (~BHE), U14.40 (~BHE), U15.40 (~BHE)
GND: C1.2, C2.2, C3.2, C4.2, C5.2, C6.2, C7.2, C8.2, C9.2, C10.2, C11.2, C12.2, C13.2, C14.2, C15.2, C16.2, C17.2, C18.2, C19.2, C20.2, C23.2, C24.2, C25.2, C28.1, C29.1, C30.1, C31.1, C32.1, J1.5, J1.10, J2.a1 (GND), J2.a2 (~PRES1), J2.a5 (GND), J2.a14 (GND), J2.a23 (GND), J2.a32 (GND), J2.b1 (GND), J2.b2 (GND), J2.b5 (GND), J2.b14 (GND), J2.b23 (GND), J2.b32 (GND), J2.c1 (GND), J2.c8 (GND), J2.c17 (GND), J2.c26 (GND), J2.c28 (GND), J2.c32 (GND), J3.a1 (GND), J3.a10 (GND), J3.b1 (GND), J3.b5 (GND), J3.b6 (~PRES), J3.b10 (GND), J3.c1 (GND), J3.c10 (GND), U1.2 (VSS_1), U1.3 (VSS_1), U1.5 (VSS_1), U1.13 (VSS_1), U1.17 (VSS_1), U1.19 (VSSPLL), U1.20 (VSS_1), U1.23 (VSS_1), U1.26 (VSS_1), U1.33 (VSS_1), U1.41 (VSS_1), U1.47 (VSS_1), U1.55 (VSS_2), U1.57 (VSS_2), U1.65 (VSS_2), U1.74 (VSS_2), U1.83 (VSS_2), U1.94 (VSS_2), U1.96 (VSS_2), U1.101 (VSS_2), U1.109 (VSS_2), U1.118 (VSS_2), U1.125 (VSS_2), U1.128 (CONF), U2.15 (GND), U3.12 (GND), U3.34 (GND), U4.12 (GND), U4.34 (GND), U5.12 (GND), U5.34 (GND), U6.12 (GND), U6.34 (GND), U7.15 (GND), U8.16 (GND), U8.17 (GND), U8.56 (GND), U8.57 (GND), U9.1 (G0), U9.2 (G1), U9.12 (~SYNC), U9.14 (B0), U9.15 (B1), U9.39 (R0), U9.40 (R1), U10.15 (GND), U11.1 (GND), U12.12 (GND), U12.34 (GND), U13.12 (GND), U13.34 (GND), U14.12 (GND), U14.34 (GND), U15.12 (GND), U15.34 (GND), U17.8 (GND), U18.15 (GND), U19.10 (GND), U20.10 (GND), U21.10 (GND), U22.10 (GND), U23.10 (GND)
GNDA: C22.2, C26.2, C27.2, J1.6, J1.7, J1.8, R3.2, RN1.1 (common), U9.25 (GND), U9.26 (GND), U9.27 (~IOB), U9.31 (~IOG), U9.33 (~IOR), U16.2 (V-)
unnamed: C21.1, U9.35 (COMP)
unnamed: R3.1, U9.37 (Rset)
unnamed: R1.2, U11.7 (VREF2), U11.8 (EN)
unnamed: C22.1, R2.2, U9.36 (Vref), U16.1 (V+)
~RAMCS0: U3.6 (~CE), U17.15 (Y0)
~RAMCS1: U4.6 (~CE), U17.14 (Y1)
~RAMCS2: U5.6 (~CE), U17.13 (Y2)
~RAMCS3: U6.6 (~CE), U17.12 (Y3)
~RAMCS4: U12.6 (~CE), U17.11 (Y4)
~RAMCS5: U13.6 (~CE), U17.10 (Y5)
~RAMCS6: U14.6 (~CE), U17.9 (Y6)
~RAMCS7: U15.6 (~CE), U17.7 (Y7)
